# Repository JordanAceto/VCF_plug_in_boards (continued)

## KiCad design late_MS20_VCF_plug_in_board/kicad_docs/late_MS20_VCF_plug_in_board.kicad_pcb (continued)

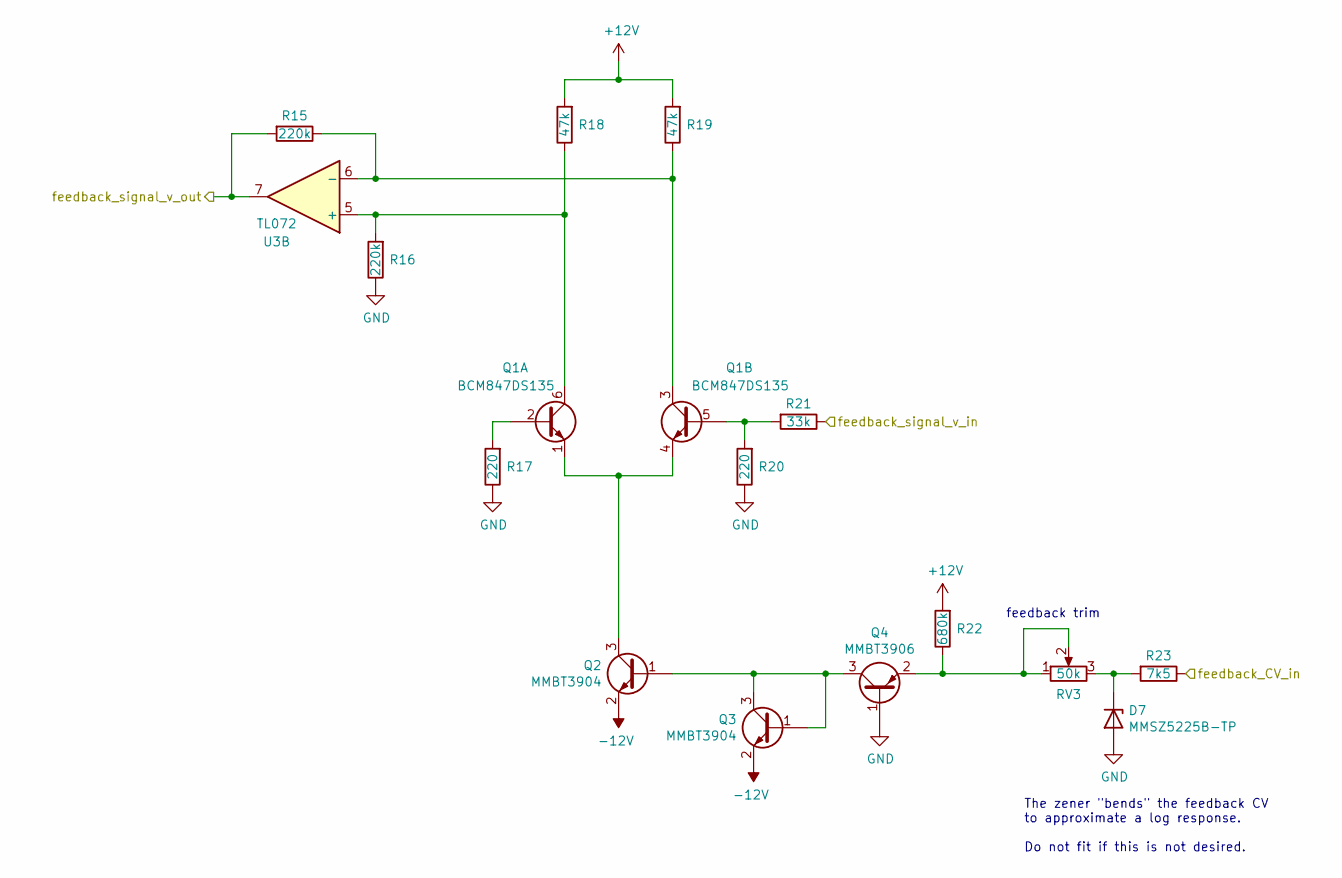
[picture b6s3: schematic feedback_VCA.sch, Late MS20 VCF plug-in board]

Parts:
D7: MMSZ5225B-TP; D_SOD-123
Q1: BCM847DS135; SOT457
Q2, Q3: MMBT3904; SOT-23_Handsoldering
Q4: MMBT3906; SOT-23_Handsoldering
R15, R16: 220k; R_0805_2012Metric_Pad1.15x1.40mm_HandSolder
R17, R20: 220; R_0805_2012Metric_Pad1.15x1.40mm_HandSolder
R18, R19: 47k; R_0805_2012Metric_Pad1.15x1.40mm_HandSolder
R21: 33k; R_0805_2012Metric_Pad1.15x1.40mm_HandSolder
R22: 680k; R_0805_2012Metric_Pad1.15x1.40mm_HandSolder
R23: 7k5; R_0805_2012Metric_Pad1.15x1.40mm_HandSolder
RV3: 50k; Potentiometer_Bourns_3296W_Vertical
U3: TL072; SOIC-8_3.9x4.9mm_P1.27mm

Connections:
+12V: R18.2, R19.2, R22.2; also elsewhere on the board
-12V: Q2.2 (E), Q3.2 (E); also elsewhere on the board
/feedback_VCA/feedback_CV_in: R23.1; also elsewhere on the board
/feedback_VCA/feedback_signal_v_in: R21.1; also elsewhere on the board
/filter_core/feedback_signal_v_in: R15.2, U3.7; also elsewhere on the board
GND: D7.2 (A), Q4.1 (B), R16.1, R17.1, R20.1; also elsewhere on the board
unnamed: D7.1 (K), R23.2, RV3.3
unnamed: Q1.1 (E), Q1.4 (E), Q2.3 (C)
unnamed: Q1.2 (B), R17.2
unnamed: Q1.3 (C), R15.1, R19.1, U3.6 (-)
unnamed: Q1.5 (B), R20.2, R21.2
unnamed: Q1.6 (C), R16.2, R18.1, U3.5 (+)
unnamed: Q2.1 (B), Q3.1 (B), Q3.3 (C), Q4.3 (C)
unnamed: Q4.2 (E), R22.1, RV3.1, RV3.2

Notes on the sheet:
The zener "bends" the feedback CV to approximate a log response. Do not fit if this is not desired.
feedback trim

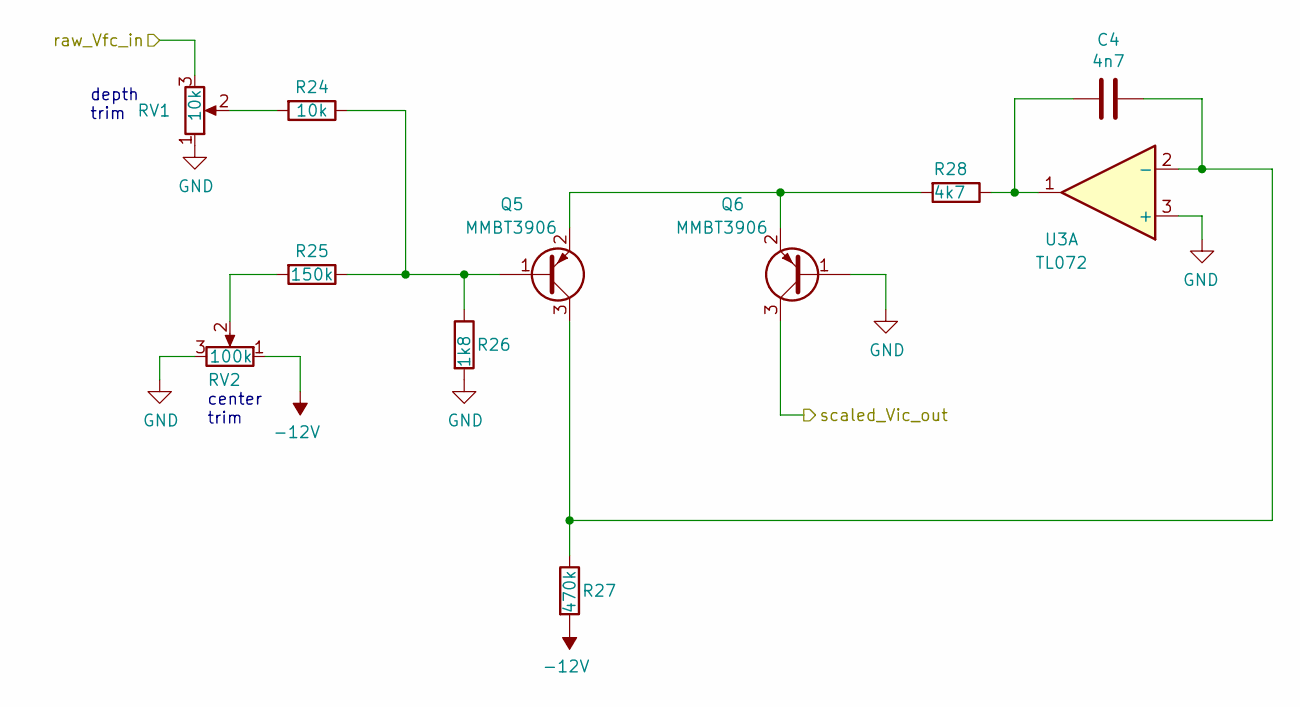
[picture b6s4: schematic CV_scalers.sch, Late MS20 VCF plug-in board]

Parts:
C4: 4n7; C_0805_2012Metric_Pad1.15x1.40mm_HandSolder
Q5, Q6: MMBT3906; SOT-23_Handsoldering
R24: 10k; R_0805_2012Metric_Pad1.15x1.40mm_HandSolder
R25: 150k; R_0805_2012Metric_Pad1.15x1.40mm_HandSolder
R26: 1k8; R_0805_2012Metric_Pad1.15x1.40mm_HandSolder
R27: 470k; R_0805_2012Metric_Pad1.15x1.40mm_HandSolder
R28: 4k7; R_0805_2012Metric_Pad1.15x1.40mm_HandSolder
RV1: 10k; Potentiometer_Bourns_3296W_Vertical
RV2: 100k; Potentiometer_Bourns_3296W_Vertical
U3: TL072; SOIC-8_3.9x4.9mm_P1.27mm

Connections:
-12V: R27.2, RV2.1; also elsewhere on the board
/CV_scalers/raw_Vfc_in: RV1.3; also elsewhere on the board
/filter_core/Vfc_in: Q6.3 (C); also elsewhere on the board
GND: Q6.1 (B), R26.2, RV1.1, RV2.3, U3.3 (+); also elsewhere on the board
unnamed: C4.1, R28.1, U3.1
unnamed: C4.2, Q5.3 (C), R27.1, U3.2 (-)
unnamed: Q5.1 (B), R24.1, R25.1, R26.1
unnamed: Q5.2 (E), Q6.2 (E), R28.2
unnamed: R24.2, RV1.2
unnamed: R25.2, RV2.2

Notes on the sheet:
depth trim
center trim

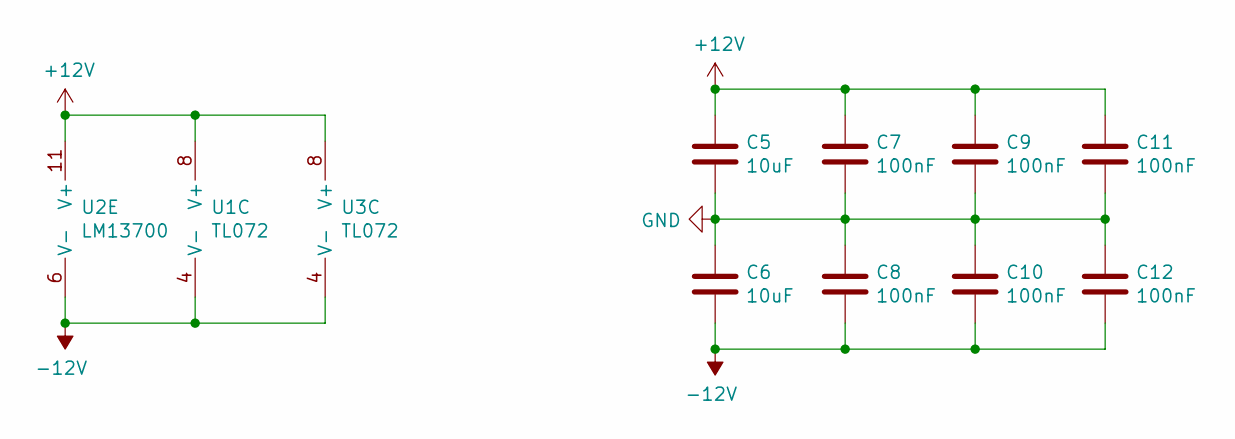
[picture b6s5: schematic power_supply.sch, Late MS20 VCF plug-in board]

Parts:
C5, C6: 10uF; C_0805_2012Metric_Pad1.15x1.40mm_HandSolder
C7, C8, C9, C10, C11, C12: 100nF; C_0805_2012Metric_Pad1.15x1.40mm_HandSolder
U1, U3: TL072; SOIC-8_3.9x4.9mm_P1.27mm
U2: LM13700; SOIC-16_3.9x9.9mm_P1.27mm

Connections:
+12V: C5.1, C7.1, C9.1, C11.1, U1.8 (V+), U2.11 (V+), U3.8 (V+); also elsewhere on the board
-12V: C6.2, C8.2, C10.2, C12.2, U1.4 (V-), U2.6 (V-), U3.4 (V-); also elsewhere on the board
GND: C5.2, C6.1, C7.2, C8.1, C9.2, C10.1, C11.2, C12.1; also elsewhere on the board

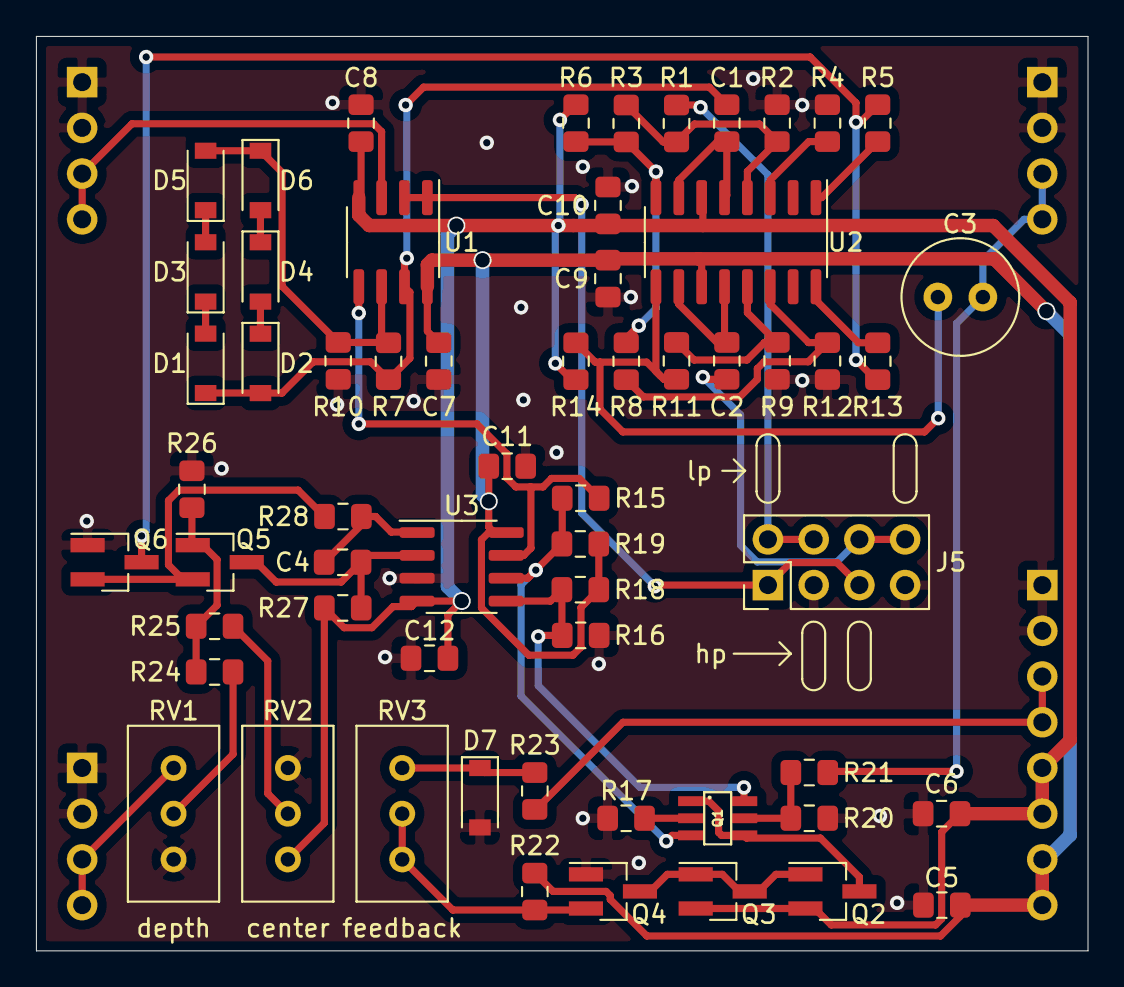
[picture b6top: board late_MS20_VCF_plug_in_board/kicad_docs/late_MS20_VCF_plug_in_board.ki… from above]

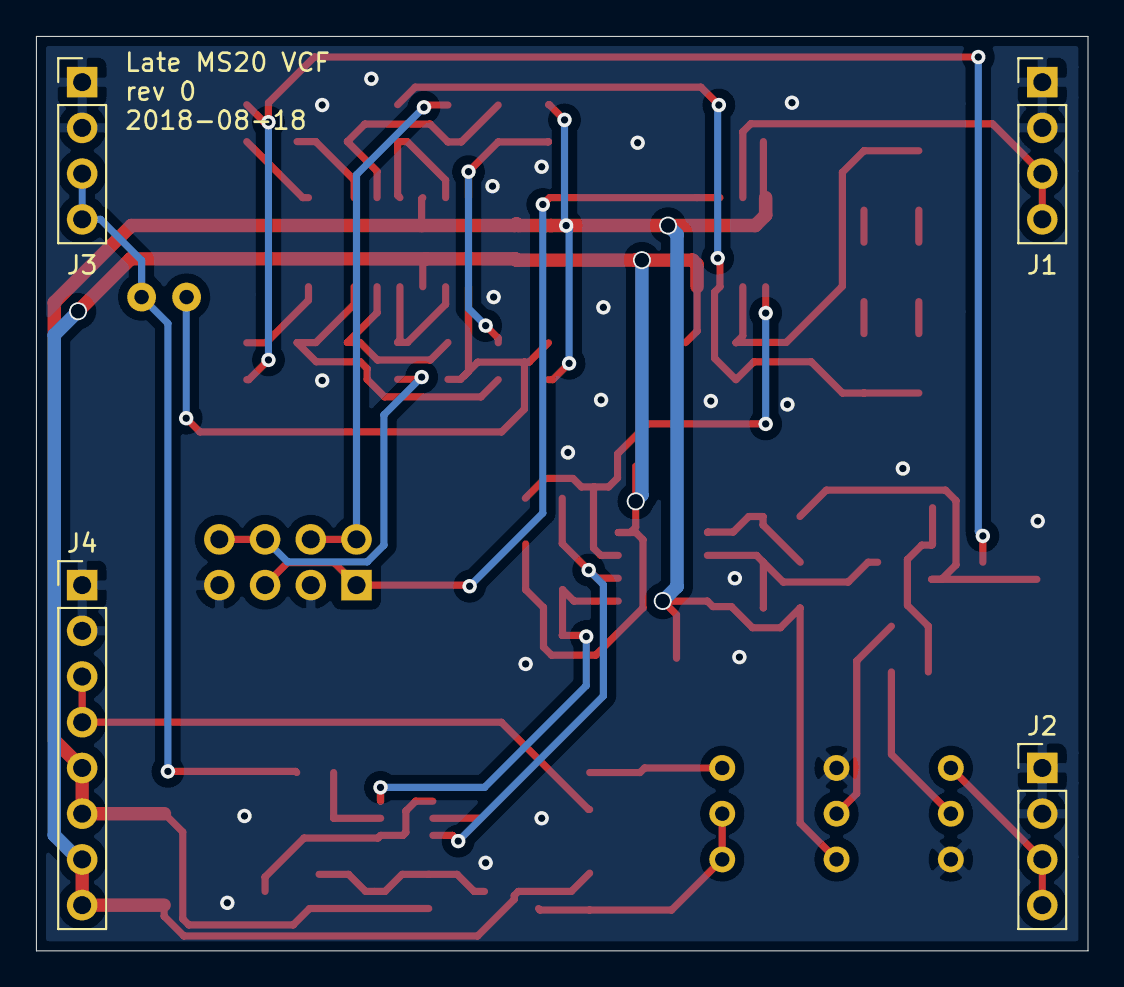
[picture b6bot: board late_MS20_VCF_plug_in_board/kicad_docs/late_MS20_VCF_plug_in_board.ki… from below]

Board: 2 copper layers, 58.4 x 50.8 mm, 64 parts (4 on the bottom side), 42 nets.

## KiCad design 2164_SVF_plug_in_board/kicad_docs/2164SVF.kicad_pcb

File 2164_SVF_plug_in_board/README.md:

# 2164 State Variable Filter Plug-In Board

Small SSM/V/SSI2164 based state variable filter PCB, designed to plug into a larger motherboard.

## Details

2164 based SVF with low pass, band pass, and high pass modes available. This PCB includes the audio path and CV inputs for frequency and feedback, but does not include any modulation sources.

The intended use for this board is to plug in to a larger motherboard which contains slots for one or more of these plug-in boards, as well as modulation sources, panel controls, and input/output routing.

## Inputs

-Audio in: dry audio input to be filtered.

-Frequency CV in: 0 volts to +2.048 volts, higher voltage = higher sweep.

-Feedback CV in: 0 volts to +2.048 volts, higher voltage = more feedback.

## Outputs

-Audio out: filtered audio output.

## Filter mode selection

- This filter has three filter modes available: Low Pass, Band Pass, and High Pass.

- One mode at a time can be selected with a jumper.

## Power Supply Requirements

A bipolar 12 volt power supply is required. This will typically come from the motherboard.

## Calibration

- See the top level README for calibration instructions.

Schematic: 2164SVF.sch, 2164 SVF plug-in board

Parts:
J1: signal_input; PinHeader_1x04_P2.54mm_Vertical
J2: cutoff_CV_input; PinHeader_1x04_P2.54mm_Vertical
J3: signal_output; PinHeader_1x04_P2.54mm_Vertical
J4: feedback_CV_and_PS; PinHeader_1x08_P2.54mm_Vertical
J5: mode_select_jumper; PinHeader_2x03_P2.54mm_Vertical

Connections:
+12V: J4.7, J4.8; also elsewhere on the board
-12V: J4.5, J4.6; also elsewhere on the board
/CV_path/FM_in: J2.3, J2.4; also elsewhere on the board
/CV_path/resonance_CV_in: J4.3, J4.4; also elsewhere on the board
/audio_path/band_pass_out: J5.3; also elsewhere on the board
/audio_path/filter_input: J1.3, J1.4; also elsewhere on the board
/audio_path/high_pass_out: J5.1; also elsewhere on the board
/audio_path/low_pass_out: J5.5; also elsewhere on the board
GND: J1.1, J1.2, J2.1, J2.2, J3.1, J3.2, J4.1, J4.2; also elsewhere on the board
unnamed: J3.3, J3.4, J5.2, J5.4, J5.6

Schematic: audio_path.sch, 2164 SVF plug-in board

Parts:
C1: 47pF; C_0805_2012Metric_Pad1.15x1.40mm_HandSolder
C2: 100pF; C_0805_2012Metric_Pad1.15x1.40mm_HandSolder
C3, C4, C7: 560pF; C_0805_2012Metric_Pad1.15x1.40mm_HandSolder
C6, C9: 220pF; timing_cap_dual_fp
D1, D2: 5z1; D_SOD-123
R4, R7, R8, R9, R10, R13, R14: 30k; R_0805_2012Metric_Pad1.15x1.40mm_HandSolder
R5: 150k; R_0805_2012Metric_Pad1.15x1.40mm_HandSolder
R6: 15k; R_0805_2012Metric_Pad1.15x1.40mm_HandSolder
R11, R12, R15: 510; R_0805_2012Metric_Pad1.15x1.40mm_HandSolder
U1, U3: TL072; SOIC-8_3.9x4.9mm_P1.27mm
U2: SSM2164; SOIC-16_3.9x9.9mm_P1.27mm

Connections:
/audio_path/Vfc_in: U2.3, U2.6; also elsewhere on the board
/audio_path/Vrez_in: U2.14; also elsewhere on the board
/audio_path/band_pass_out: C6.1, D2.1 (K), R5.1, R13.1, R14.2, U1.7; also elsewhere on the board
/audio_path/filter_input: R4.2; also elsewhere on the board
/audio_path/high_pass_out: R8.1, R10.2, U1.1; also elsewhere on the board
/audio_path/low_pass_out: C1.1, C9.1, R7.1, U3.7; also elsewhere on the board
GND: C3.2, C4.2, C7.2, U1.3 (+), U1.5 (+), U2.10, U3.3 (+), U3.5 (+); also elsewhere on the board
unnamed: C1.2, R4.1, R5.2, R6.2, R7.2, R8.2, U1.2 (-)
unnamed: C2.1, R9.1, U2.13, U3.2 (-)
unnamed: C2.2, R6.1, R9.2, U3.1
unnamed: C3.1, R11.1
unnamed: C4.1, R12.1
unnamed: C6.2, D1.1 (K), U1.6 (-), U2.4
unnamed: C7.1, R15.1
unnamed: C9.2, U2.5, U3.6 (-)
unnamed: D1.2 (A), D2.2 (A)
unnamed: R10.1, R11.2, U2.2
unnamed: R12.2, R13.2, U2.15
unnamed: R14.1, R15.2, U2.7

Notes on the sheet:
unused

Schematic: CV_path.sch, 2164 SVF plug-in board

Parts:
C11: 100pF; C_0805_2012Metric_Pad1.15x1.40mm_HandSolder
D3, D4: 1N4148W; D_SOD-123
D5: BAT48; D_SOD-123
R16: 20k; R_0805_2012Metric_Pad1.15x1.40mm_HandSolder
R18: 68k; R_0805_2012Metric_Pad1.15x1.40mm_HandSolder
R19: 22k; R_0805_2012Metric_Pad1.15x1.40mm_HandSolder
RV1, RV2, RV3: 10k; Potentiometer_Bourns_3296W_Vertical
U4: TL072; SOIC-8_3.9x4.9mm_P1.27mm

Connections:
-12V: RV2.1; also elsewhere on the board
/CV_path/FM_in: RV1.3; also elsewhere on the board
/CV_path/resonance_CV_in: RV3.3; also elsewhere on the board
/audio_path/Vfc_in: C11.1, D4.1 (K), R19.1; also elsewhere on the board
/audio_path/Vrez_in: D5.1 (K); also elsewhere on the board
GND: RV1.1, RV2.3, RV3.1, U4.3 (+); also elsewhere on the board
unnamed: C11.2, D3.2 (A), R16.1, R18.1, R19.2, U4.2 (-)
unnamed: D3.1 (K), D4.2 (A), U4.1
unnamed: D5.2 (A), U4.6 (-), U4.7
unnamed: R16.2, RV1.2
unnamed: R18.2, RV2.2
unnamed: RV3.2, U4.5 (+)

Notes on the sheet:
offset trim
feedback trim
Cutoff frequency CV scaler
Resonance CV scaler
approximately 0 volts to +1 volts
approximately +2 volts to 0 volts
depth trim

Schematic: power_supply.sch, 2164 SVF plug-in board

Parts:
C14, C15: 10uF; CP_Elec_6.3x5.4_Nichicon
C17, C18, C19, C20, C21, C22, C24, C25: 100nF; C_0805_2012Metric_Pad1.15x1.40mm_HandSolder
D6: BAT48; D_SOD-123
R25: opt; R_0805_2012Metric_Pad1.15x1.40mm_HandSolder
U1, U3, U4: TL072; SOIC-8_3.9x4.9mm_P1.27mm
U2: SSM2164; SOIC-16_3.9x9.9mm_P1.27mm

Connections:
+12V: C14.1, C17.1, C19.1, C21.1, C24.1, R25.1, U1.8 (V+), U2.16 (V+), U3.8 (V+), U4.8 (V+); also elsewhere on the board
-12V: C15.2, C18.2, C20.2, C22.2, C25.2, D6.2 (A), U1.4 (V-), U2.9 (V-), U3.4 (V-), U4.4 (V-); also elsewhere on the board
GND: C14.2, C15.1, C17.2, C18.1, C19.2, C20.1, C21.2, C22.1, C24.2, C25.1, D6.1 (K), U2.8 (gnd); also elsewhere on the board
unnamed: R25.2, U2.1 (mode)

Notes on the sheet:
2164 protection
optional class A/AB mode resistor
TL072 power connections
SSM2164 power connections
Decoupling capacitors

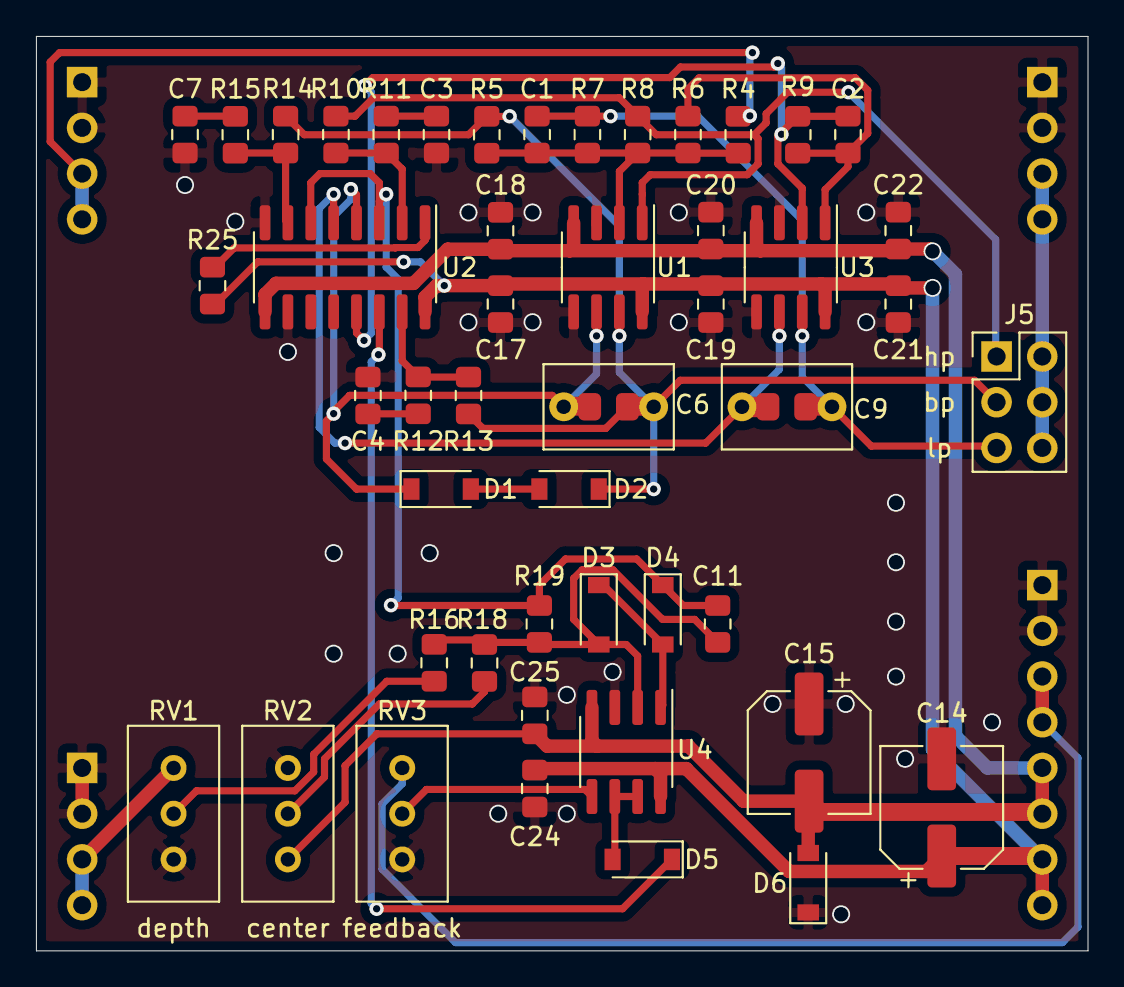
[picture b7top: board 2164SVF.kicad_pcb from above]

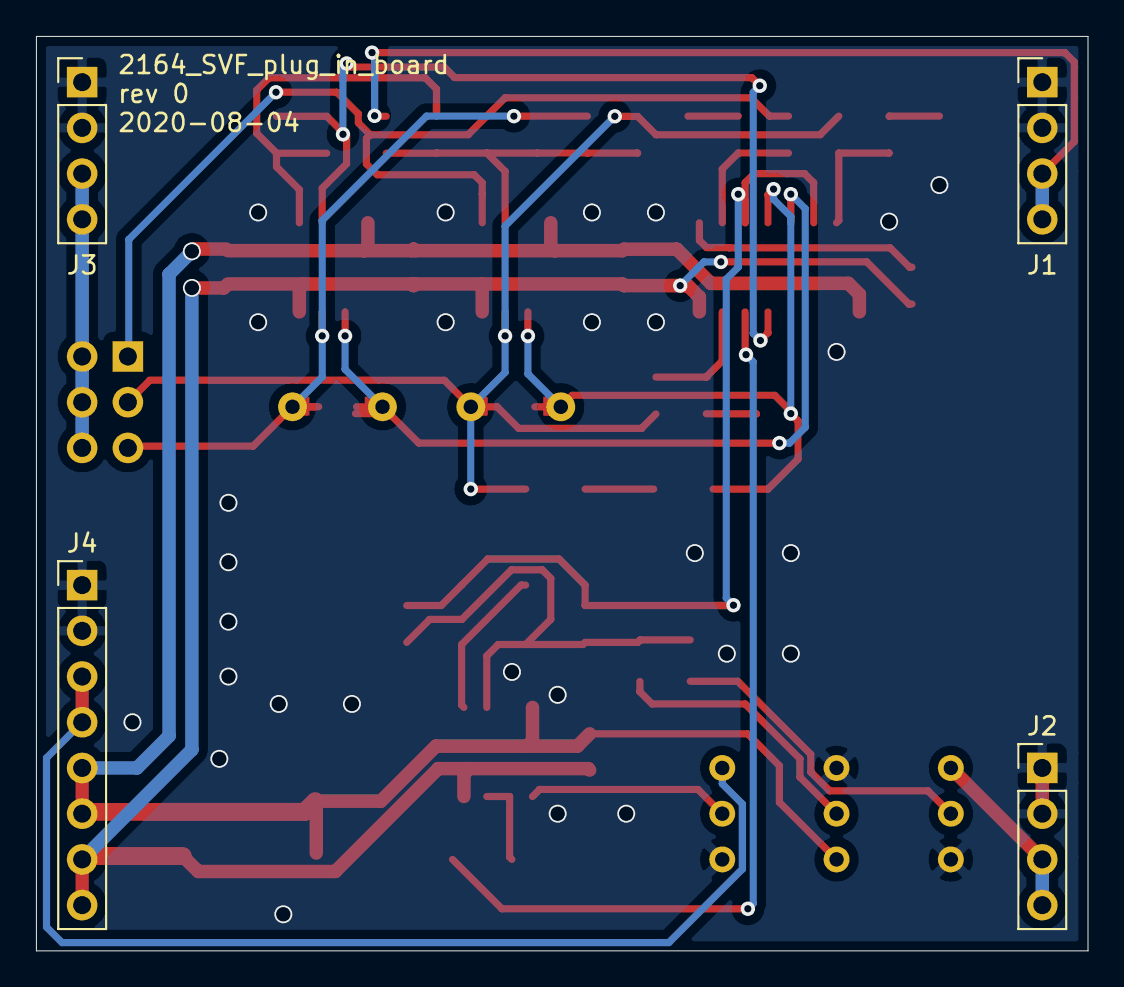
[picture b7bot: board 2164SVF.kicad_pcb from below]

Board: 2 copper layers, 58.4 x 50.8 mm, 52 parts (4 on the bottom side), 31 nets.

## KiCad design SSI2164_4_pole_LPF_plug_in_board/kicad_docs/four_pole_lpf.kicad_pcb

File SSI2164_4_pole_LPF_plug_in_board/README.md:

## SSI2164 4-pole Low Pass Filter plug-in board

Small SSI2164 based low pass filter PCB, designed to plug into a larger motherboard.

## Details

This pcb is set up as an "experimenters board" for trying out the 2 and 4-pole band-pass feedback as a means of Q-compensation in application note AN701. Various feedback configurations are possible, and the exact configuration is left up to the builder.

Voltage controlled feedback is provided, consistent with the other filter plug-in boards.

## Inputs

-Audio in: dry audio input to be filtered.

-Frequency CV in: 0 volts to +2.048 volts, higher voltage = higher sweep.

-Feedback CV in: 0 volts to +2.048 volts, higher voltage = more feedback.

## Outputs

-Audio out: filtered audio output.

## Power Supply Requirements

A bipolar 12 volt power supply is required. This will typically come from the motherboard.

## Calibration

- See the top level README for calibration instructions.

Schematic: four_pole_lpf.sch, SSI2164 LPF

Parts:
J1: signal_in; PinHeader_1x04_P2.54mm_Vertical
J2: CV_in; PinHeader_1x04_P2.54mm_Vertical
J3: signal_out; PinHeader_1x04_P2.54mm_Vertical
J4: feedback_CV_and_power; PinHeader_1x08_P2.54mm_Vertical

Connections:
+12V: J4.7, J4.8; also elsewhere on the board
-12V: J4.5, J4.6; also elsewhere on the board
/CV_scaler/raw_Vfc_in: J2.3, J2.4; also elsewhere on the board
/dry_signal: J1.3, J1.4; also elsewhere on the board
/feedback_VCA/4_pole_v_in: J3.3, J3.4; also elsewhere on the board
/feedback_VCA/feedback_CV_in: J4.3, J4.4; also elsewhere on the board
GND: J1.1, J1.2, J2.1, J2.2, J3.1, J3.2, J4.1, J4.2; also elsewhere on the board

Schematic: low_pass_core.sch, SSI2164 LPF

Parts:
C1: opt; C_0805_2012Metric_Pad1.15x1.40mm_HandSolder
C2, C4, C6, C8: 220pF; C_0805_2012Metric_Pad1.15x1.40mm_HandSolder
C3, C5, C7: 1n5; C_0805_2012Metric_Pad1.15x1.40mm_HandSolder
D1, D2: 1N4148W; D_SOD-123
Q1: MMBT3904; SOT-23_Handsoldering
Q2: MMBT3906; SOT-23_Handsoldering
R1, R4, R5: opt; R_0805_2012Metric_Pad1.15x1.40mm_HandSolder
R2, R7: 510; R_0805_2012Metric_Pad1.15x1.40mm_HandSolder
R3, R6, R8, R10, R11, R13, R14, R16: 15k; R_0805_2012Metric_Pad1.15x1.40mm_HandSolder
R9, R12, R15: 180; R_0805_2012Metric_Pad1.15x1.40mm_HandSolder
U1: SSM2164; SOIC-16_3.9x9.9mm_P1.27mm
U2, U3: TL072; SOIC-8_3.9x4.9mm_P1.27mm

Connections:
/dry_signal: R3.2; also elsewhere on the board
/feedback_VCA/1_pole_v_in: C2.1, R6.1, R8.2, U2.1; also elsewhere on the board
/feedback_VCA/2_pole_v_in: C4.1, R10.1, R11.2, U3.1; also elsewhere on the board
/feedback_VCA/3_pole_v_in: C6.1, R13.1, R14.2, U3.7; also elsewhere on the board
/feedback_VCA/4_pole_v_in: C8.1, R16.1, U2.7; also elsewhere on the board
/low_pass_core/Vfc: U1.3, U1.6, U1.11, U1.14; also elsewhere on the board
/low_pass_core/feedback_signal_v_in: R7.1; also elsewhere on the board
GND: C1.1, C3.1, C5.1, C7.1, Q1.2 (E), Q2.2 (E), R2.2, U2.3 (+), U2.5 (+), U3.3 (+), U3.5 (+); also elsewhere on the board
unnamed: C1.2, R5.1
unnamed: C2.2, U1.5, U2.2 (-)
unnamed: C3.2, R9.1
unnamed: C4.2, U1.4, U3.2 (-)
unnamed: C5.2, R12.1
unnamed: C6.2, U1.13, U3.6 (-)
unnamed: C7.2, R15.1
unnamed: C8.2, U1.12, U2.6 (-)
unnamed: D1.1 (K), Q1.3 (C)
unnamed: D1.2 (A), D2.1 (K), R1.1, R4.2, R7.2
unnamed: D2.2 (A), Q2.3 (C)
unnamed: Q1.1 (B), Q2.1 (B), R1.2, R2.1
unnamed: R3.1, R4.1, R5.2, R6.2, U1.7
unnamed: R8.1, R9.2, R10.2, U1.2
unnamed: R11.1, R12.2, R13.2, U1.15
unnamed: R14.1, R15.2, R16.2, U1.10

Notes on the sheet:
this network sets the feedback amplitude
For "opt" values see AN701

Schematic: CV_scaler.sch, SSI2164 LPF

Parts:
C9: 100pF; C_0805_2012Metric_Pad1.15x1.40mm_HandSolder
D5, D6: 1N4148W; D_SOD-123
R17: 100k; R_0805_2012Metric_Pad1.15x1.40mm_HandSolder
R18: 820k; R_0805_2012Metric_Pad1.15x1.40mm_HandSolder
R19: 150k; R_0805_2012Metric_Pad1.15x1.40mm_HandSolder
RV1, RV2: 10k; Potentiometer_Bourns_3296W_Vertical
U4: TL072; SOIC-8_3.9x4.9mm_P1.27mm

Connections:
-12V: RV2.1; also elsewhere on the board
/CV_scaler/raw_Vfc_in: RV1.3; also elsewhere on the board
/low_pass_core/Vfc: C9.1, D6.1 (K), R19.1; also elsewhere on the board
GND: RV1.1, RV2.3, U4.3 (+), U4.5 (+); also elsewhere on the board
unnamed: C9.2, D5.2 (A), R17.1, R18.1, R19.2, U4.2 (-)
unnamed: D5.1 (K), D6.2 (A), U4.1
unnamed: R17.2, RV1.2
unnamed: R18.2, RV2.2
unnamed: U4.6 (-), U4.7

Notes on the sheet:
scale trim
offset trim
unused

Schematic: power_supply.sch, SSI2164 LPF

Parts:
C10, C11: 10uF; C_0805_2012Metric_Pad1.15x1.40mm_HandSolder
C12, C13, C14, C15, C16, C17, C18, C19, C20, C21: 100nF; C_0805_2012Metric_Pad1.15x1.40mm_HandSolder
D4: BAT48; D_SOD-123
R20: opt; R_0805_2012Metric_Pad1.15x1.40mm_HandSolder
U1: SSM2164; SOIC-16_3.9x9.9mm_P1.27mm
U2, U3, U4, U5: TL072; SOIC-8_3.9x4.9mm_P1.27mm

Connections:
+12V: C10.1, C12.1, C14.1, C16.1, C18.1, C20.1, R20.1, U1.16 (V+), U2.8 (V+), U3.8 (V+), U4.8 (V+), U5.8 (V+); also elsewhere on the board
-12V: C11.2, C13.2, C15.2, C17.2, C19.2, C21.2, D4.2 (A), U1.9 (V-), U2.4 (V-), U3.4 (V-), U4.4 (V-), U5.4 (V-); also elsewhere on the board
GND: C10.2, C11.1, C12.2, C13.1, C14.2, C15.1, C16.2, C17.1, C18.2, C19.1, C20.2, C21.1, D4.1 (K), U1.8 (gnd); also elsewhere on the board
unnamed: R20.2, U1.1 (mode)

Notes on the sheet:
2164 protection diode
optional class A/AB resistor leave open for class AB

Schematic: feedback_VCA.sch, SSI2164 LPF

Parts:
C22: 10uF; C_Radial_D6.3mm_H5.0mm_P2.50mm
D3: MMSZ5225B; D_SOD-123
JP1: wet_polarity_jumper; SolderJumper-3_P1.3mm_Open_RoundedPad1.0x1.5mm
JP2: dry_polarity_jumper; SolderJumper-3_P1.3mm_Open_RoundedPad1.0x1.5mm
Q3: BCM847DS135; SOT457
Q4, Q5: MMBT3904; SOT-23_Handsoldering
Q6: MMBT3906; SOT-23_Handsoldering
R21, R22: 220k; R_0805_2012Metric_Pad1.15x1.40mm_HandSolder
R23, R26: 220; R_0805_2012Metric_Pad1.15x1.40mm_HandSolder
R24, R25: 47k; R_0805_2012Metric_Pad1.15x1.40mm_HandSolder
R27: 680k; R_0805_2012Metric_Pad1.15x1.40mm_HandSolder
R28: 82k; R_0805_2012Metric_Pad1.15x1.40mm_HandSolder
R29: 10k; R_0805_2012Metric_Pad1.15x1.40mm_HandSolder
R30: 7k5; R_0805_2012Metric_Pad1.15x1.40mm_HandSolder
R31, R32, R33, R34, R35: opt; R_0805_2012Metric_Pad1.15x1.40mm_HandSolder
RV3: 50k; Potentiometer_Bourns_3296W_Vertical
U5: TL072; SOIC-8_3.9x4.9mm_P1.27mm

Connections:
+12V: R24.2, R25.2, R27.2; also elsewhere on the board
-12V: Q4.2 (E), Q5.2 (E); also elsewhere on the board
/dry_signal: R35.2; also elsewhere on the board
/feedback_VCA/1_pole_v_in: R31.2; also elsewhere on the board
/feedback_VCA/2_pole_v_in: R32.2; also elsewhere on the board
/feedback_VCA/3_pole_v_in: R33.2; also elsewhere on the board
/feedback_VCA/4_pole_v_in: R34.1; also elsewhere on the board
/feedback_VCA/feedback_CV_in: R30.1; also elsewhere on the board
/low_pass_core/feedback_signal_v_in: C22.2; also elsewhere on the board
GND: D3.2 (A), Q6.1 (B), R22.1, R23.1, R26.1, U5.3 (+); also elsewhere on the board
unnamed: C22.1, R21.2, U5.7
unnamed: JP1.1 (A), JP2.1 (A), Q3.2 (B), R23.2
unnamed: JP1.2 (C), R28.2
unnamed: JP1.3 (B), JP2.3 (B), Q3.5 (B), R26.2
unnamed: JP2.2 (C), R35.1
unnamed: Q3.1 (E), Q3.4 (E), Q4.3 (C)
unnamed: Q3.3 (C), R22.2, R24.1, U5.5 (+)
unnamed: Q3.6 (C), R21.1, R25.1, U5.6 (-)
unnamed: Q4.1 (B), Q5.1 (B), Q5.3 (C), Q6.3 (C)
unnamed: R28.1, R29.1, U5.1
unnamed: R29.2, R31.1, R32.1, R33.1, R34.2, U5.2 (-)

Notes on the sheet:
The zener "bends" the feedback CV to approximate a log response. Do not fit if this is not desired.
feedback trim
The weighted sum of the lpf coefficients accomplishes "Q-compensation" which makes it so that increasing feedback does not result in passband attenuation. See AN701 for two different setups: 4th order bandpass feedback, or 2nd order bandpass feedback. Note that the feedback signal polarity must als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

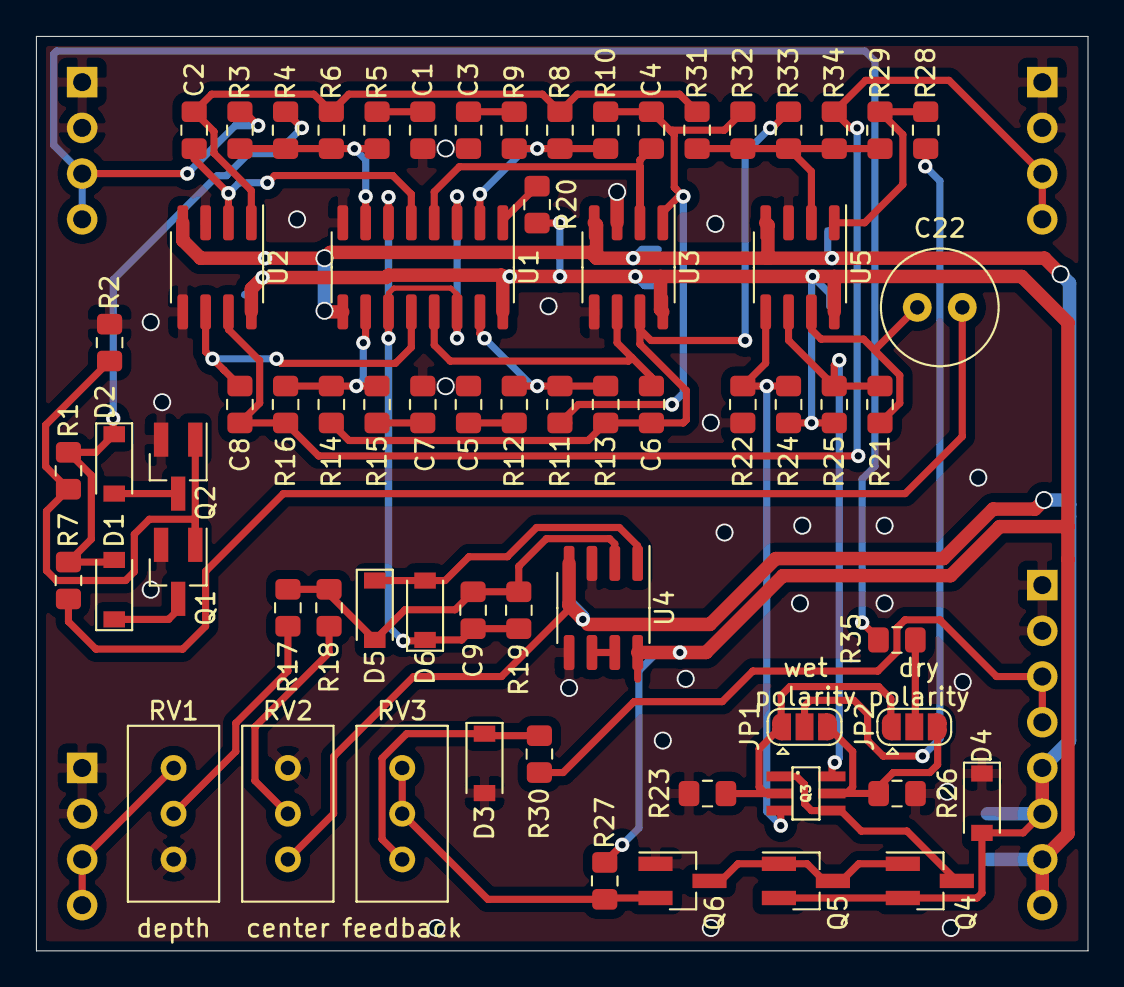
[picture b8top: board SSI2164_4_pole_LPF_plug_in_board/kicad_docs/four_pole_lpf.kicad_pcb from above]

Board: 2 copper layers, 58.4 x 50.8 mm, 83 parts (16 on the bottom side), 47 nets.

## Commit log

2020-08-01 Create LICENSE
2020-08-01 remove erroneous check for 2164LPF pcb layout
2020-08-01 clean up CEM3320 LPF, add smd cap footprints for timing caps
2020-08-01 update mutron-III pcb
2020-08-01 add some mutron-III pics
2020-08-01 add readme
2020-08-01 tick off some mutron-III checkmarks
2020-08-02 generate schematic
2020-08-02 generate BOM
2020-08-02 generate gerbers
2020-08-02 swap j2 and j1 positions for consistency
2020-08-02 regenerate gerbers after j1/j2 swap
2020-08-02 generate minimoog VCF gerbers
2020-08-02 add minimoog VCF pics
2020-08-02 add minimoog VCF readme
2020-08-02 add missing designator to schematic note
2020-08-04 add links to boards in readme status section
2020-08-04 fix copy-paste error
2020-08-10 add template for starting new projects
2020-08-10 update readme for addition of template
2020-08-13 change zener value
2020-08-13 fix schemo and pcb problems
2020-08-13 check of CEM3320 VCF
2020-08-13 add pic and note about mutron-III SVF vactrol options
2020-08-13 remove trimmer direction from readme
2020-08-14 add calibration instructions to main readme
2020-08-14 move calibration to top level readme
2020-08-14 change zener
2020-08-14 check off mutron-III build
2020-08-14 update readme with project structure info
2020-08-14 check off minimoog VCF
2020-08-17 progress on SSI2164 LPF
2020-08-18 flip trimpots to be consistent with other boards
2020-08-18 update pics after trimpot flip
2020-08-18 flip trimpots for consistency
2020-08-18 add 2164 SVF board
2020-08-18 move BOM to correct location
2020-08-19 zip gerbers
2020-08-19 add rendered pics
2020-08-19 add late MS20 stlye VCF board
2020-08-19 add MS20 VCF files
2020-08-19 add MS20 checklist to readme
2020-08-28 change Fcv offset trim resistor
2020-08-29 change 2164 SVF zeners
2020-08-29 tick off 2164 SVF after successful build
2020-08-29 change late MS20 CV scaling
2020-08-29 update late MS20 for hp/lp jumper config
2020-08-29 tick off late MS20 after successful build
2020-10-24 tick of ARP4072 LPF in readme after building and testing
2021-08-13 check off SSI LPF after successful build
2021-12-16 update 2164 LPF, better feedback VCA
2021-12-16 update readme with new 2164 LPF link
2021-12-16 update 2164 phasor board
2021-12-30 rename 2164 phasor build docs
2022-05-29 Add SSI2140 LPF board
2022-05-29 Add rest of SSI2140 LPF files
2022-05-29 Add SSI2140 LPF to main readme
2022-07-11 Update gitignore
2022-07-11 Update readme, check boxes after successful test builds
2022-08-19 Update minimoog PPF, better feedback VCA, better docs
2022-08-19 Update late MS20 VCF, better feedback VCA, better docs
